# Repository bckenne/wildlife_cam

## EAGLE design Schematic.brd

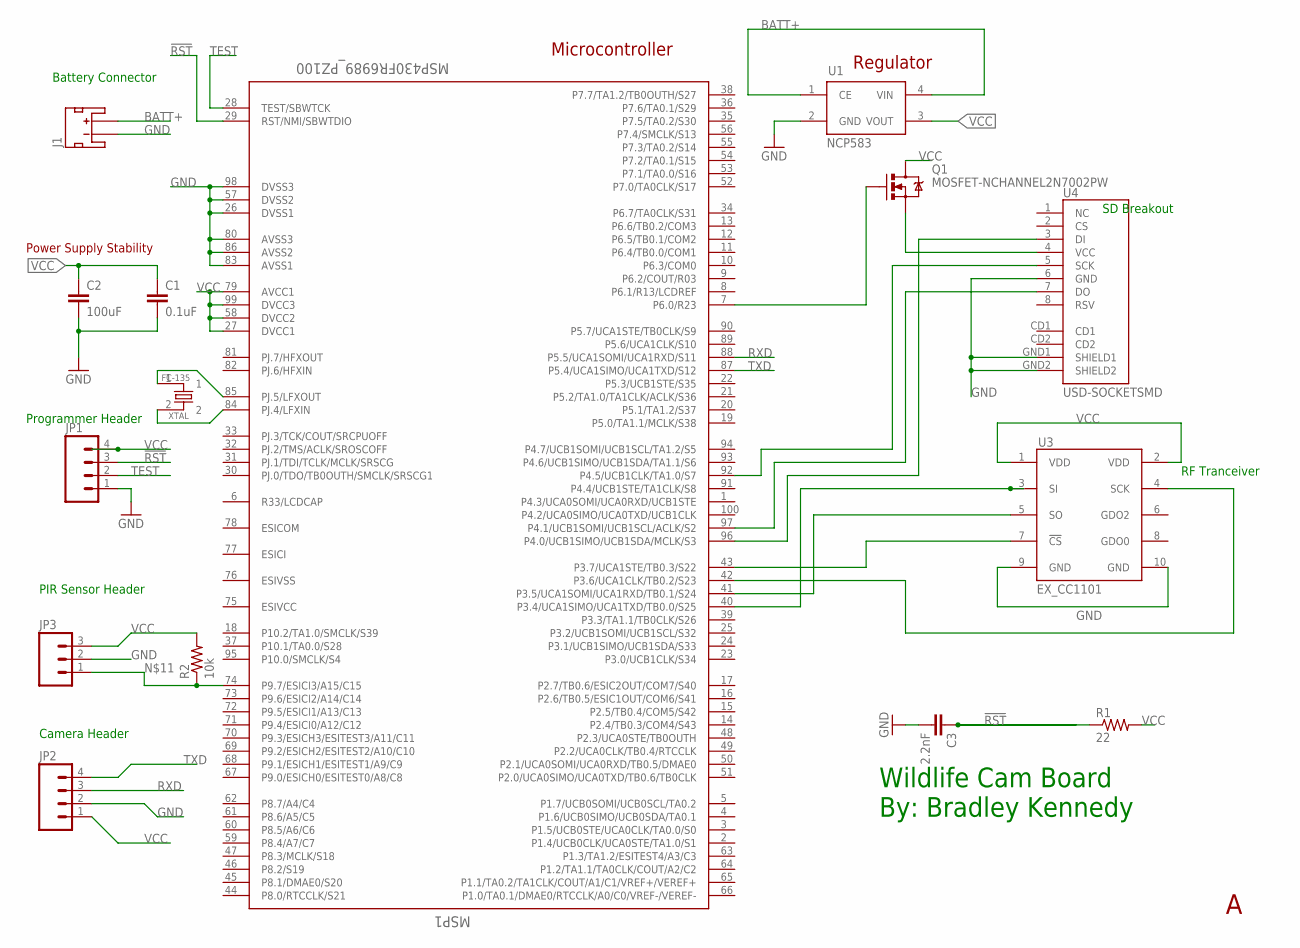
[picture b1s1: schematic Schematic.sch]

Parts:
C1: 0.1uF; 0805
C2: 100uF; 0805
C3: 2.2nF; 0805
J1: JST_2MM_MALE; JST-2-SMD
JP1, JP2: M04PTH; 1X04
JP3: M03PTH; 1X03
MSP1: MSP430FR6989_PZ100; PZ100
Q1: MOSFET-NCHANNEL2N7002PW; SOT323
R1: 22; 0603-RES
R2: 10k; AXIAL-0.3EZ
U1: NCP583; SC82-AB_1PRIMARY
U3: EX_CC1101; 2X5
U4: USD-SOCKETSMD; MICRO-SD-SOCKET-PP
XTAL: FC-135; FC-135_1PRIMARY

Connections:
!RST: C3.1, JP1.3, MSP1.29 (RST/NMI/SBWTDIO), R1.1
BATT+: J1.2 (+), U1.1 (CE), U1.4 (VIN)
CLK: MSP1.42 (P3.6/UCA1CLK/TB0.2/S23), U3.4 (SCK)
GND: C1.2, C2.2, C3.2, J1.1 (-), JP1.1, JP2.2, JP3.2, MSP1.26 (DVSS1), MSP1.57 (DVSS2), MSP1.80 (AVSS3), MSP1.83 (AVSS1), MSP1.86 (AVSS2), MSP1.98 (DVSS3), U1.2 (GND), U3.9 (GND), U3.10 (GND), U4.6 (GND), U4.GND1 (SHIELD1), U4.GND2 (SHIELD2)
unnamed: MSP1.40 (P3.4/UCA1SIMO/UCA1TXD/TB0.0/S25), U3.3 (SI)
unnamed: MSP1.97 (P4.1/UCB1SOMI/UCB1SCL/ACLK/S2), U4.7 (DO)
unnamed: MSP1.96 (P4.0/UCB1SIMO/UCB1SDA/MCLK/S3), U4.3 (DI)
unnamed: MSP1.84 (PJ.4/LFXIN), XTAL.2
unnamed: MSP1.85 (PJ.5/LFXOUT), XTAL.1
unnamed: MSP1.43 (P3.7/UCA1STE/TB0.3/S22), U3.7 (!CS)
unnamed: Q1.2 (S), U4.4 (VCC)
unnamed: MSP1.7 (P6.0/R23), Q1.1 (G)
unnamed: MSP1.92 (P4.5/UCB1CLK/TA1.0/S7), U4.5 (SCK)
unnamed: JP3.1, MSP1.74 (P9.7/ESICI3/A15/C15), R2.P$1 (1)
unnamed: MSP1.41 (P3.5/UCA1SOMI/UCA1RXD/TB0.1/S24), U3.5 (SO)
RXD: JP2.3, MSP1.88 (P5.5/UCA1SOMI/UCA1RXD/S11)
TEST: JP1.2, MSP1.28 (TEST/SBWTCK)
TXD: JP2.4, MSP1.87 (P5.4/UCA1SIMO/UCA1TXD/S12)
VCC: C1.1, C2.1, JP1.4, JP2.1, JP3.3, MSP1.27 (DVCC1), MSP1.58 (DVCC2), MSP1.79 (AVCC1), MSP1.99 (DVCC3), Q1.3 (D), R1.2, R2.P$2 (2), U1.3 (VOUT), U3.1 (VDD), U3.2 (VDD)

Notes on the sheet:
Regulator
Power Supply Stability
Microcontroller
Battery Connector
Programmer Header
Camera Header
PIR Sensor Header
SD Breakout
Wildlife Cam Board By: Bradley Kennedy
RF Tranceiver

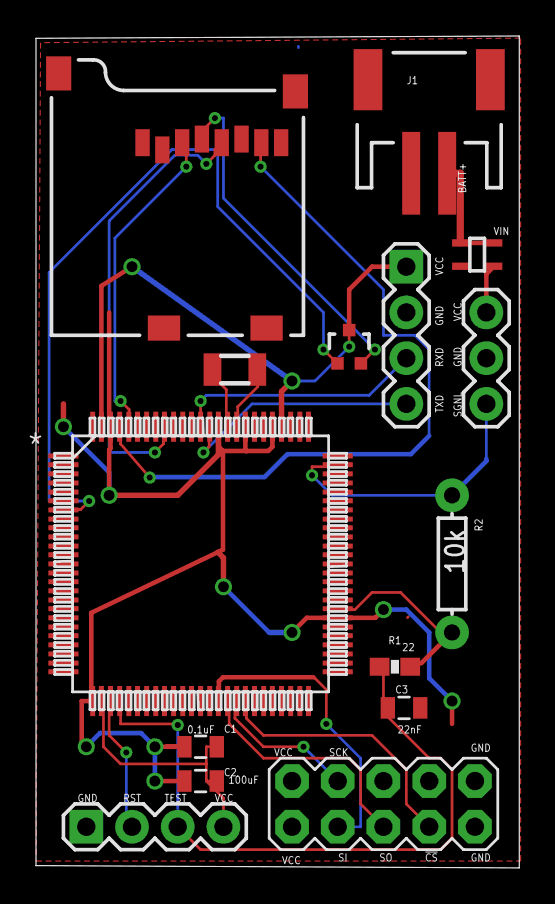
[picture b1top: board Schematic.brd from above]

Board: 2 copper layers, 26.8 x 46.2 mm, 15 parts (0 on the bottom side), 19 nets.

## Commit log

2016-01-07 adding all files
2016-01-07 deleted readme.md

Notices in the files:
parts and their libraries:
SparkFun-Capacitors: Licensing: CC v3.0 Share-Alike You are welcome to use this library for commercial purposes.
SparkFun-Connectors: Licensing: Creative Commons ShareAlike 4.0 International - https://creativecommons.org/licenses/by-sa/4.0
